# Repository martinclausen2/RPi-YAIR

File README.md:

# RPi-YAIR
Raspberry Pi YAIR (Yet Another Internet Radio)

Diverted from [Raspberry Pi YAIR - Yet Another Internet Radio](https://www.mikrocontroller.net/articles/Raspberry_Pi_YAIR_(Yet_Another_Internet_Radio) )

German parts to be translated later. Details on one particular hardware setup to be found under articel cited above.

### Einleitung

Ja, es gibt sie: Internetradios. Zum Kaufen. Zum Selbst bauen. Aus Routern. Aus dem Raspberry Pi. Aber schlussendlich gefiel mir keines so gut, dass es mich vom Selbstbau abgehalten hätte ...
### Features für den Nutzer

* Intuitive Bedienung über zwei Drehencoder mit Tastfunktion
  * Dynamische Schrittweitenanpassung für die schnelle und genaue Einstellung der Lautstärke und Sender
* Fernbedienbar via IR-Fernbedieung oder Netzwerk / WLAN via Smartphone
* Sehr niedriger Standby-Stromverbrauch
* Lesen der Musik via Netzwerk oder empfang via BT

### Hardware Setup

* Basis Raspberry Pi Zero (nur headless) oder besser, 512MB, WLAN und BT
* I2S Audio DAC connection please see [External-Non-USB-Audio-DAC-ES9023,-PCM5102,-etc.](https://github.com/MiczFlor/RPi-Jukebox-RFID/wiki/External-Non-USB-Audio-DAC-ES9023,-PCM5102,-etc.)
* Microcontroller connnection please see [Raspberry Pi YAIR - Yet Another Internet Radio](https://www.mikrocontroller.net/articles/Raspberry_Pi_YAIR_(Yet_Another_Internet_Radio) )

## MCU

Die Software besteht aus folgenden Teilen:

* Hauptschleife
  * Setzt Zustände der State-Machines in Befehle, die über den UART gesendet werden, um
  * Steuert die Stromversorgung von Raspberry Pi, Monitor und Audio-Verstärker

* Interrupt-Routinen
  * RC5 Decoder, ausgelöst durch Timer 0 bei 4,5kHz, jeden 9. Aufruf wird auch der Drehencoder ausgewertet
  * Einlesen der Tasten, ausgelöst durch Timer aus RTC der MCU bei 10Hz

* Initialisierung der MCU
  * Core Funktionen, hauptsächliche Stromsparfunktionen
  * I/O Pins
  * Interne RTC als 10Hz Taktgeber: 6*10^6/4/128/10
  * UART: 57600 Bit/s Mode 1
  * Watchdog wird abgeschaltet
  * Interrupts freischalten

* Auswertung Drehencoder

* RC5 Decoder

Der RC5 Decoder beruht auf einer State-Machine, die schrittweise die einzelnen Bits erkennt und dann in Adresse und Daten zerlegt. Nach der Erkennung eines kompletten Kommandos wird steht rCounter auf dem Wert 12 und das Hauptprogramm beginnt mit der Decodierung (Aufruf "DecodeRemote()").

Die Software kann per #define in Quellcode für LPC922 oder LPC93X kompiliert werden. Die zusätzlichen Funktionsblöcke der LPC93X werden nicht verwendet. Als Kompiler ist SDCC zu verwenden.

Bei Bedarf könnte ich MCUs programmieren. Alternativ ist der Code sicher leicht auf einen AVR, STM32, oder ... zu portieren. 

## Raspberry Pi Setup

### Step by Step Instructions

Please follow the follwoing steps to steup the raspberry pi

* deploy raspberry pi os bookworm on sdcard
* setup the configuration 'sudo raspi-config'
  * setup system options
    * WLAN
    * Hostname
  * Interface
    * SSH
    * Serail Port - enable serial port, but not (!) console
  * Localisation Options
    * Timezone
    * Keyboard
    * WLAN Country
  * Advanced Options
    * Expand Filesystem
* update repos `sudo apt-get update`
* update software `sudo apt-get dist-upgrade`
* install software `sudo apt-get install mpd mpc wakeonlan git`
* Reboot Rpi
* Adjust configuration files from RPi folder and changes dummy credentials, consider to modifiy the following files on your traget system in case your installation has other specifics.  
  * `/boot/firmware/cmdline.txt`
    * remove `console=tty1`
  * `/boot/firmware/config.txt`
    * remove `dtparam=audio=on` by addin a hash in fromt of the line
    * add `dtoverlay=hifiberry-dac`
  * If you decide to adjust the start volue, you need to do it in `receiver.c`, complie again, and in `startmpd.sh`
* Copy adjusted configuration files to RPi
* Install BT audio receiver
  * `git clone https://github.com/nicokaiser/rpi-audio-receiver.git`
  * `cd rpi-audio-receiver`
  * Choose the features as needed when running `./install.sh`
* create folder to mount music folder from NAS
  * `mkdir /media/music`
  * `chmod 555 /media/music`
* Make playlist folder accessable `sudo chmod 777 /var/lib/mpd/playlists`
  * Deploy there at least `radio.m3u`, this is used for playback at startup (entry 4)
* stop automated concole activation
  * details may depend on your sprecific RPi model and configuration
	* use `systemctl status` to check for any serial-getty services running and deactivte them using stop, disable, mask
  * `sudo systemctl stop serial-getty@ttyAMA0.service`
  * `sudo systemctl disable serial-getty@ttyAMA0.service`
  * `sudo systemctl mask serial-getty@ttyAMA0.service`
  * `sudo systemctl stop serial-getty@tty1.service`
  * `sudo systemctl disable serial-getty@tty1.service`
  * `sudo systemctl mask serial-getty@tty1.service`
  * `sudo systemctl stop serial-getty@ttyS0.service`
  * `sudo systemctl disable serial-getty@ttyS0.service`
  * `sudo systemctl mask serial-getty@ttyS0.service`
* Activate services
  * `sudo systemctl enable mpd`
  * `sudo systemctl enable wol`
  * `sudo systemctl enable startmpd`
  * `sudo systemctl enable receiver`
  * `sudo systemctl daemon-reload`
* Compile software to receive data from MCU
  * `gcc receiver.c -o receiver`
  * `chmod 755 receiver`
  * If you test the software on console, make sure to delete temp file in `/tmp/mpdlist` before tring to start the service
### Debugging
* Review audio interfaces by
  * `cat /proc/asound/modules`
  * `cat /proc/asound/cards`
* Review service status
  * `systemctl status`
  * `systemctl [status servicename]`
* Review system logs
  * `journalctl -rm -n 1000`
* Inspect data from MCU
  * install minicom `sudo apt-get install minicom`
  * `mincom --device /dev/tytyS0 --baudrate 57600`

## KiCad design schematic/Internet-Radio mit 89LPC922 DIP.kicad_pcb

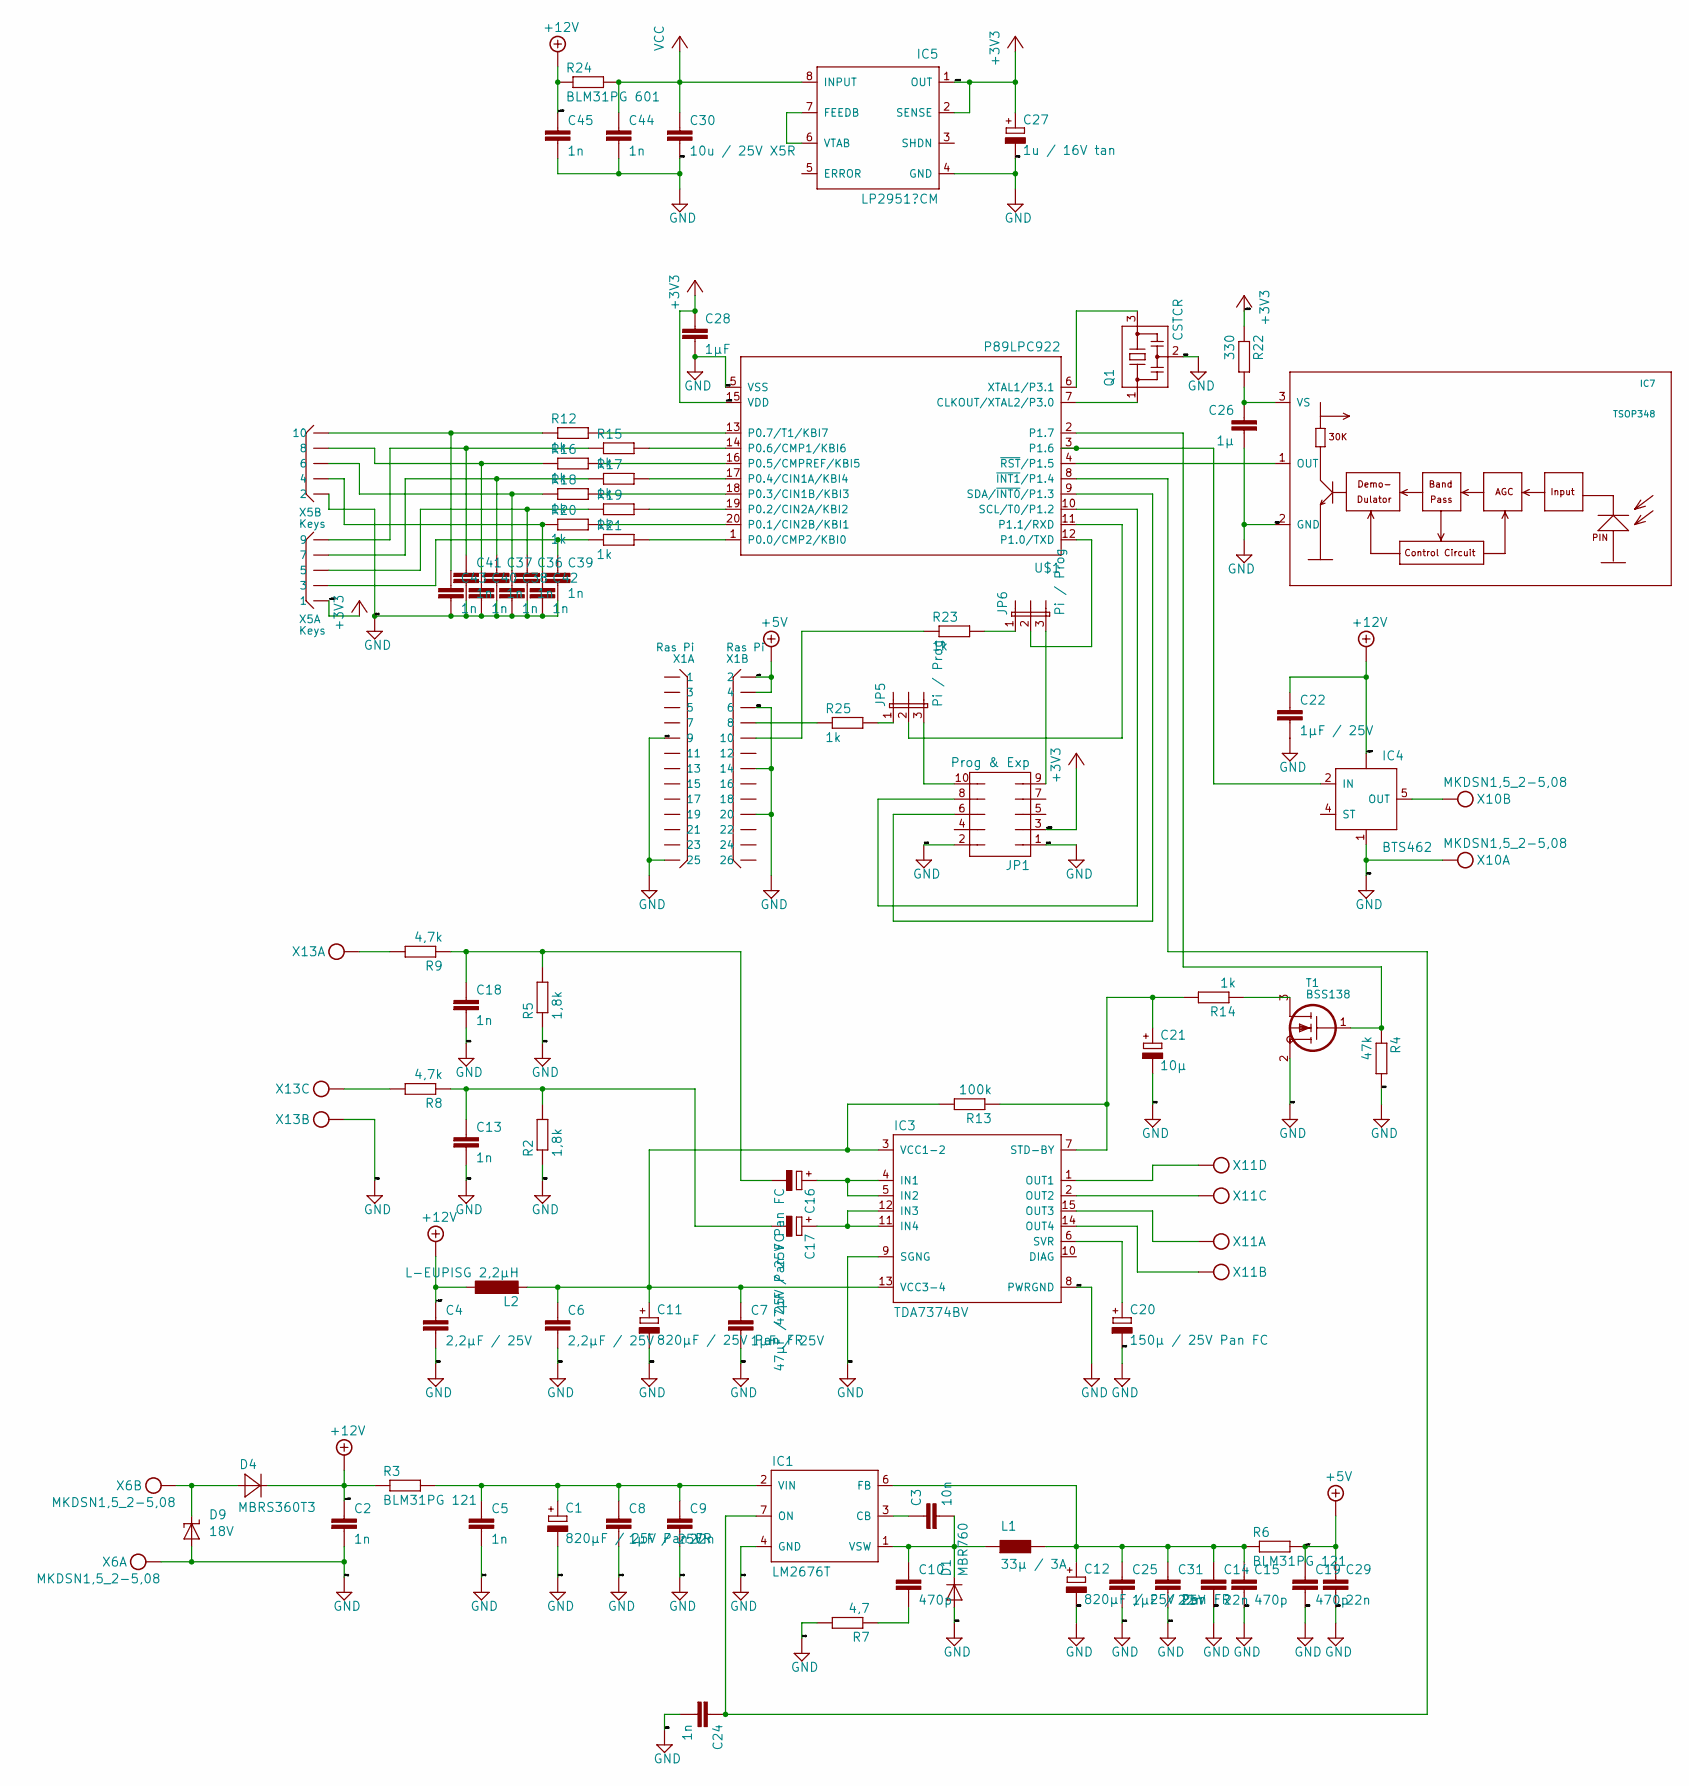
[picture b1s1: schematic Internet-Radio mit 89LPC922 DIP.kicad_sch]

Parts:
C1, C11, C12: 820µF / 25V Pan FR; TT5D10
C2, C5, C13, C18, C24, C44, C45: 1n; C0805
C3: 10n; C0805
C4, C6: 2,2µF / 25V; C0805
C7, C8, C22, C25: 1µF / 25V; C0805
C9, C14, C29, C31: 22n; C0805
C10, C15, C19: 470p; C0805
C16, C17: 47µF / 25V Pan FC; E2,5-5
C20: 150µ / 25V Pan FC; E3,5-8
C21: 10µ; E2,5-5
C26: 1µ; C0805
C27: 1u / 16V tan; CT3216
C28: 1µF; C0805
C30: 10u / 25V X5R; C1206
C36, C37, C38, C39, C40, C41, C42, C43: 1n; C0603
D1: MBR760; TO220ACS
D4: MBRS360T3; SMC
D9: 18V; SMBJ
IC1: LM2676T; TO220-7
IC3: TDA7374BV; MULTIWATT-15V
IC4: BTS462; TO252-5-11
IC5: LP2951?CM; SO-08
IC7: TSOP348
JP1: Prog & Exp; JP5Q
JP5, JP6: Pi / Prog; JP2
L1: 33µ / 3A; PIS4728
L2: L-EUPISG 2,2µH; PISG
Q1: CSTCR; CSTCR6M
R2, R5: 1,8k; R1206
R3, R6: BLM31PG 121; R1206
R4: 47k; R1206
R7: 4,7; R1206
R8, R9: 4,7k; R1206
R12, R14, R15, R16, R17, R18, R19, R20, R21, R23, R25: 1k; R1206
R13: 100k; R1206
R22: 330; R1206
R24: BLM31PG 601; R1206
T1: BSS138; SOT23
U$1: P89LPC922; DIL20
X1: Ras Pi; X26N-IDC
X5: Keys; X10N-IDC
X6: MKDSN1,5_2-5,08
X10: MKDSN1,5_2-5,08; MPN MKDSN 1,5/2-5.08
X11: MKDSN1,5_4-5,08
X13: MKDSN1,5_3-5,08

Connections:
+3V3: C27.+, C28.1, IC5.1 (OUT), IC5.2 (SENSE), JP1.3, R22.1, U$1.15 (VDD), X5.1
+5V: C19.1, C29.1, R6.2, X1.2, X1.4
+12V: C2.1, C4.1, C22.1, C45.1, D4.C, IC4.TAB (VBB), L2.1, R3.1, R24.1
GND: C1.-, C2.2, C4.2, C5.2, C6.2, C7.2, C8.2, C9.2, C11.-, C12.-, C13.2, C14.2, C15.2, C18.2, C19.2, C20.-, C21.-, C22.2, C24.2, C25.2, C26.2, C27.-, C28.2, C29.2, C30.2, C31.2, C36.2, C37.2, C38.2, C39.2, C40.2, C41.2, C42.2, C43.2, C44.2, C45.2, D1.A, D9.A, IC1.4 (GND), IC3.8 (PWRGND), IC3.9 (SGNG), IC4.1 (GND), IC5.4 (GND), IC7.2 (GND), JP1.1, JP1.2, Q1.2, R2.1, R4.2, R5.1, R7.2, T1.2 (S), U$1.5 (VSS), X1.6, X1.9, X1.14, X1.20, X1.25, X5.2, X6.1, X10.1, X13.2
unnamed: C1.+, C5.1, C8.1, C9.1, IC1.2 (VIN), R3.2
unnamed: C3.1, IC1.3 (CB)
unnamed: C3.2, C10.1, D1.C, IC1.1 (VSW), L1.P$1
unnamed: C10.2, R7.1
unnamed: C6.1, C7.1, C11.+, IC3.3 (VCC1-2), IC3.13 (VCC3-4), L2.2, R13.2
unnamed: C12.+, C14.1, C15.1, C25.1, C31.1, IC1.6 (FB), L1.P$2, R6.1
unnamed: C13.1, C17.-, R2.2, R8.1
unnamed: C16.+, IC3.4 (IN1), IC3.5 (IN2)
unnamed: C16.-, C18.1, R5.2, R9.1
unnamed: C17.+, IC3.11 (IN4), IC3.12 (IN3)
unnamed: C20.+, IC3.6 (SVR)
unnamed: C21.+, IC3.7 (STD-BY), R13.1, R14.2
unnamed: C24.1, IC1.7 (ON), U$1.8 (~INT1/P1.4)
unnamed: C26.1, IC7.3 (VS), R22.2
unnamed: C36.1, R19.1, X5.5
unnamed: C37.1, R17.1, X5.7
unnamed: C38.1, R18.1, X5.6
unnamed: C39.1, R21.1, X5.3
unnamed: C40.1, R16.1, X5.8
unnamed: C41.1, R15.1, X5.9
unnamed: C42.1, R20.1, X5.4
unnamed: C43.1, R12.1, X5.10
unnamed: D4.A, D9.C, X6.2
unnamed: IC3.1 (OUT1), X11.4
unnamed: IC3.2 (OUT2), X11.3
unnamed: IC3.14 (OUT4), X11.2
unnamed: IC3.15 (OUT3), X11.1
unnamed: IC4.2 (IN), U$1.3 (P1.6)
unnamed: IC4.5 (OUT), X10.2
unnamed: IC5.6 (VTAB), IC5.7 (FEEDB)
unnamed: IC7.1 (OUT), U$1.4 (~RST/P1.5)
unnamed: JP1.6, U$1.9 (SDA/~INT0/P1.3)
unnamed: JP1.8, U$1.10 (SCL/T0/P1.2)
unnamed: JP1.9, JP6.3
unnamed: JP1.10, JP5.3
unnamed: JP5.1, R25.2
unnamed: JP5.2, U$1.11 (P1.1/RXD)
unnamed: JP6.1, R23.2
unnamed: JP6.2, U$1.12 (P1.0/TXD)
unnamed: Q1.1, U$1.7 (CLKOUT/XTAL2/P3.0)
unnamed: Q1.3, U$1.6 (XTAL1/P3.1)
unnamed: R4.1, T1.1 (G), U$1.2 (P1.7)
unnamed: R8.2, X13.3
unnamed: R9.2, X13.1
unnamed: R12.2, U$1.13 (P0.7/T1/KBI7)
unnamed: R14.1, T1.3 (D)
unnamed: R15.2, U$1.14 (P0.6/CMP1/KBI6)
unnamed: R16.2, U$1.16 (P0.5/CMPREF/KBI5)
unnamed: R17.2, U$1.17 (P0.4/CIN1A/KBI4)
unnamed: R18.2, U$1.18 (P0.3/CIN1B/KBI3)
unnamed: R19.2, U$1.19 (P0.2/CIN2A/KBI2)
unnamed: R20.2, U$1.20 (P0.1/CIN2B/KBI1)
unnamed: R21.2, U$1.1 (P0.0/CMP2/KBI0)
unnamed: R23.1, X1.10
unnamed: R25.1, X1.8
VCC: C30.1, C44.1, IC5.8 (INPUT), R24.2

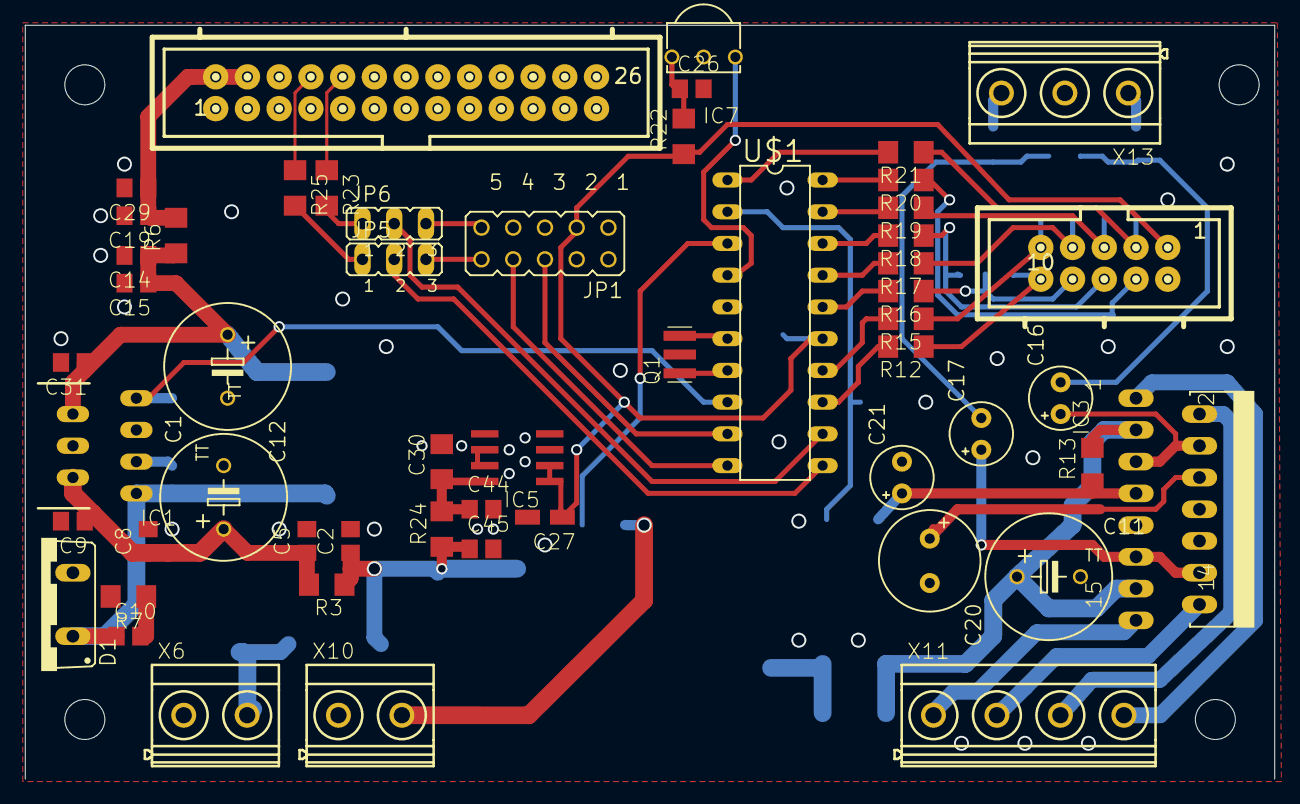
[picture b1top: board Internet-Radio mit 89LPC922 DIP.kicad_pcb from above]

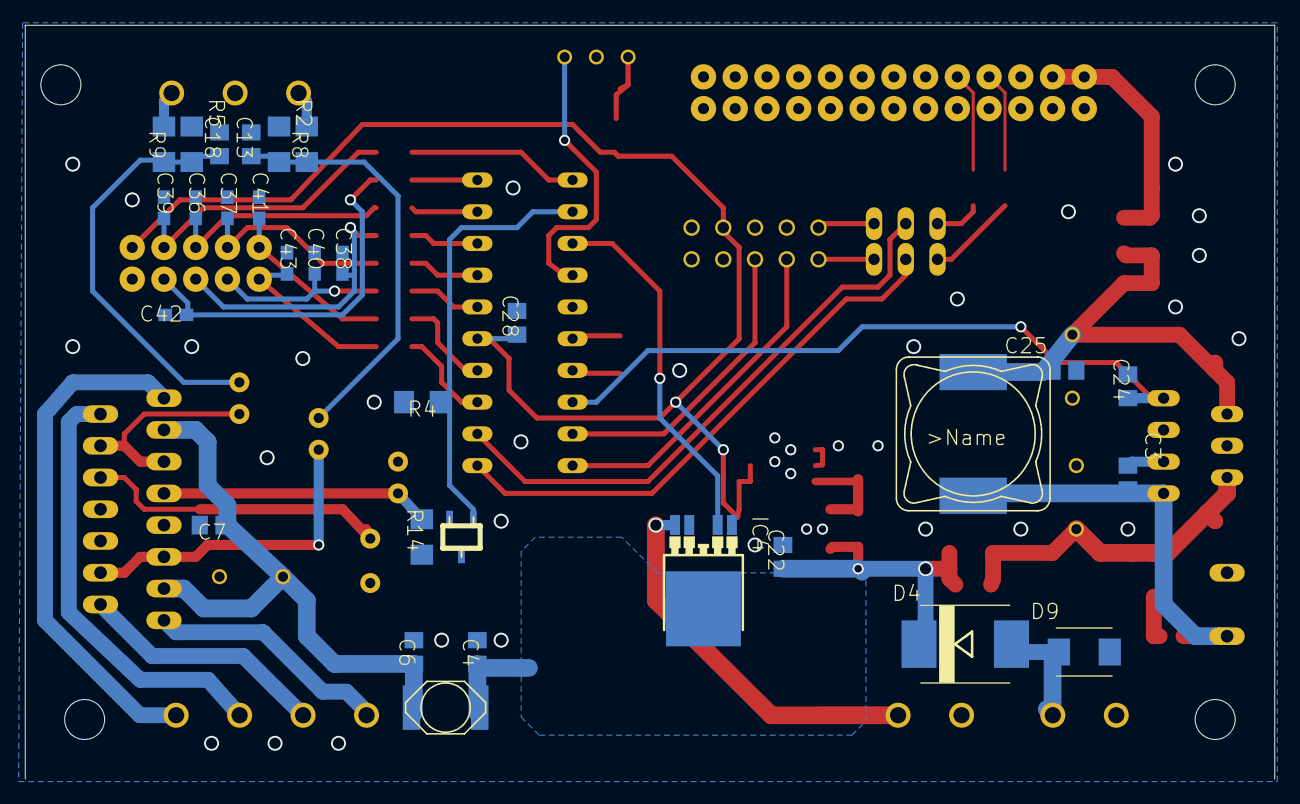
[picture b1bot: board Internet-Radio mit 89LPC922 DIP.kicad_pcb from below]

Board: 2 copper layers, 100.0 x 60.3 mm, 88 parts (30 on the bottom side), 60 nets.

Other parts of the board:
@HOLE0, @HOLE1, @HOLE2, @HOLE3: (no value)

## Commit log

2024-02-11 Inital commit
2024-02-11 added schematics
2024-02-11 add debugging help reduced rights of startmpd.service
2024-02-11 fix sporadic activation of HDMI without connected device
2024-02-23 removed reading of mpd play list - not required anymore
